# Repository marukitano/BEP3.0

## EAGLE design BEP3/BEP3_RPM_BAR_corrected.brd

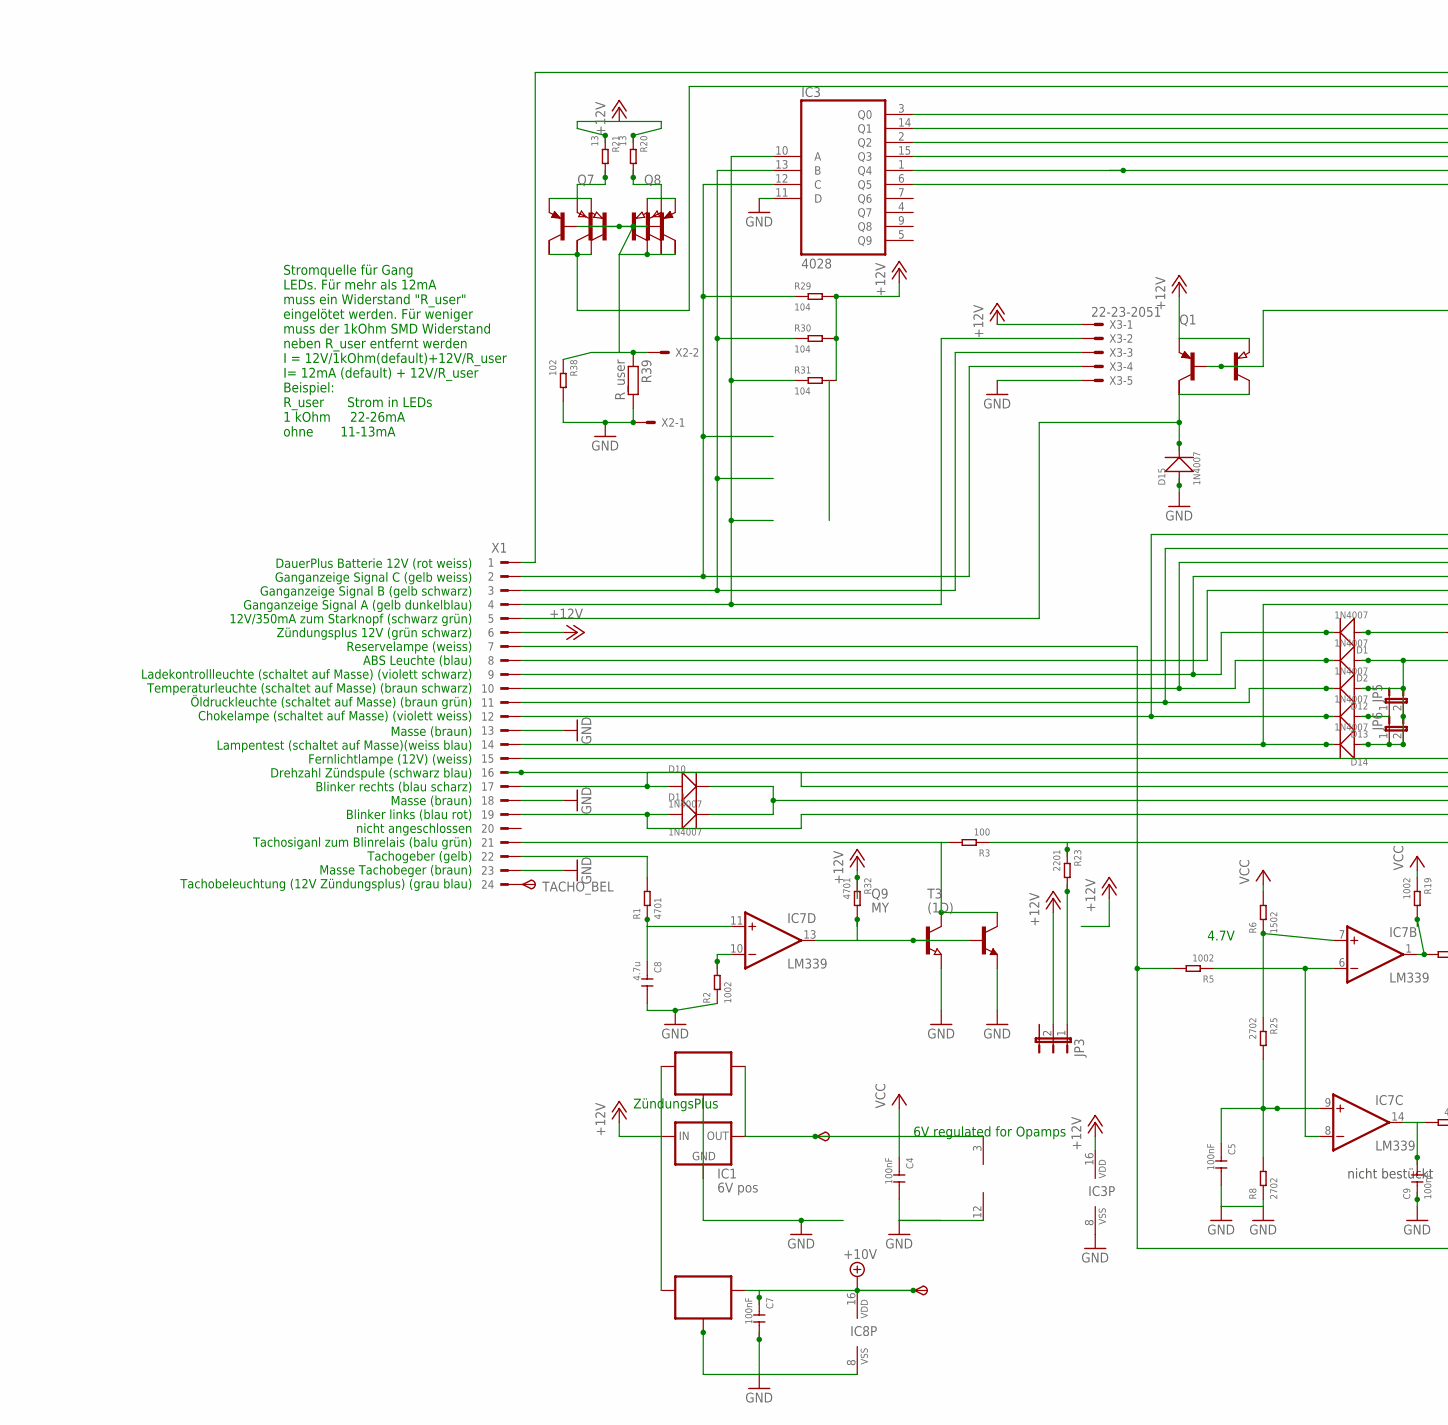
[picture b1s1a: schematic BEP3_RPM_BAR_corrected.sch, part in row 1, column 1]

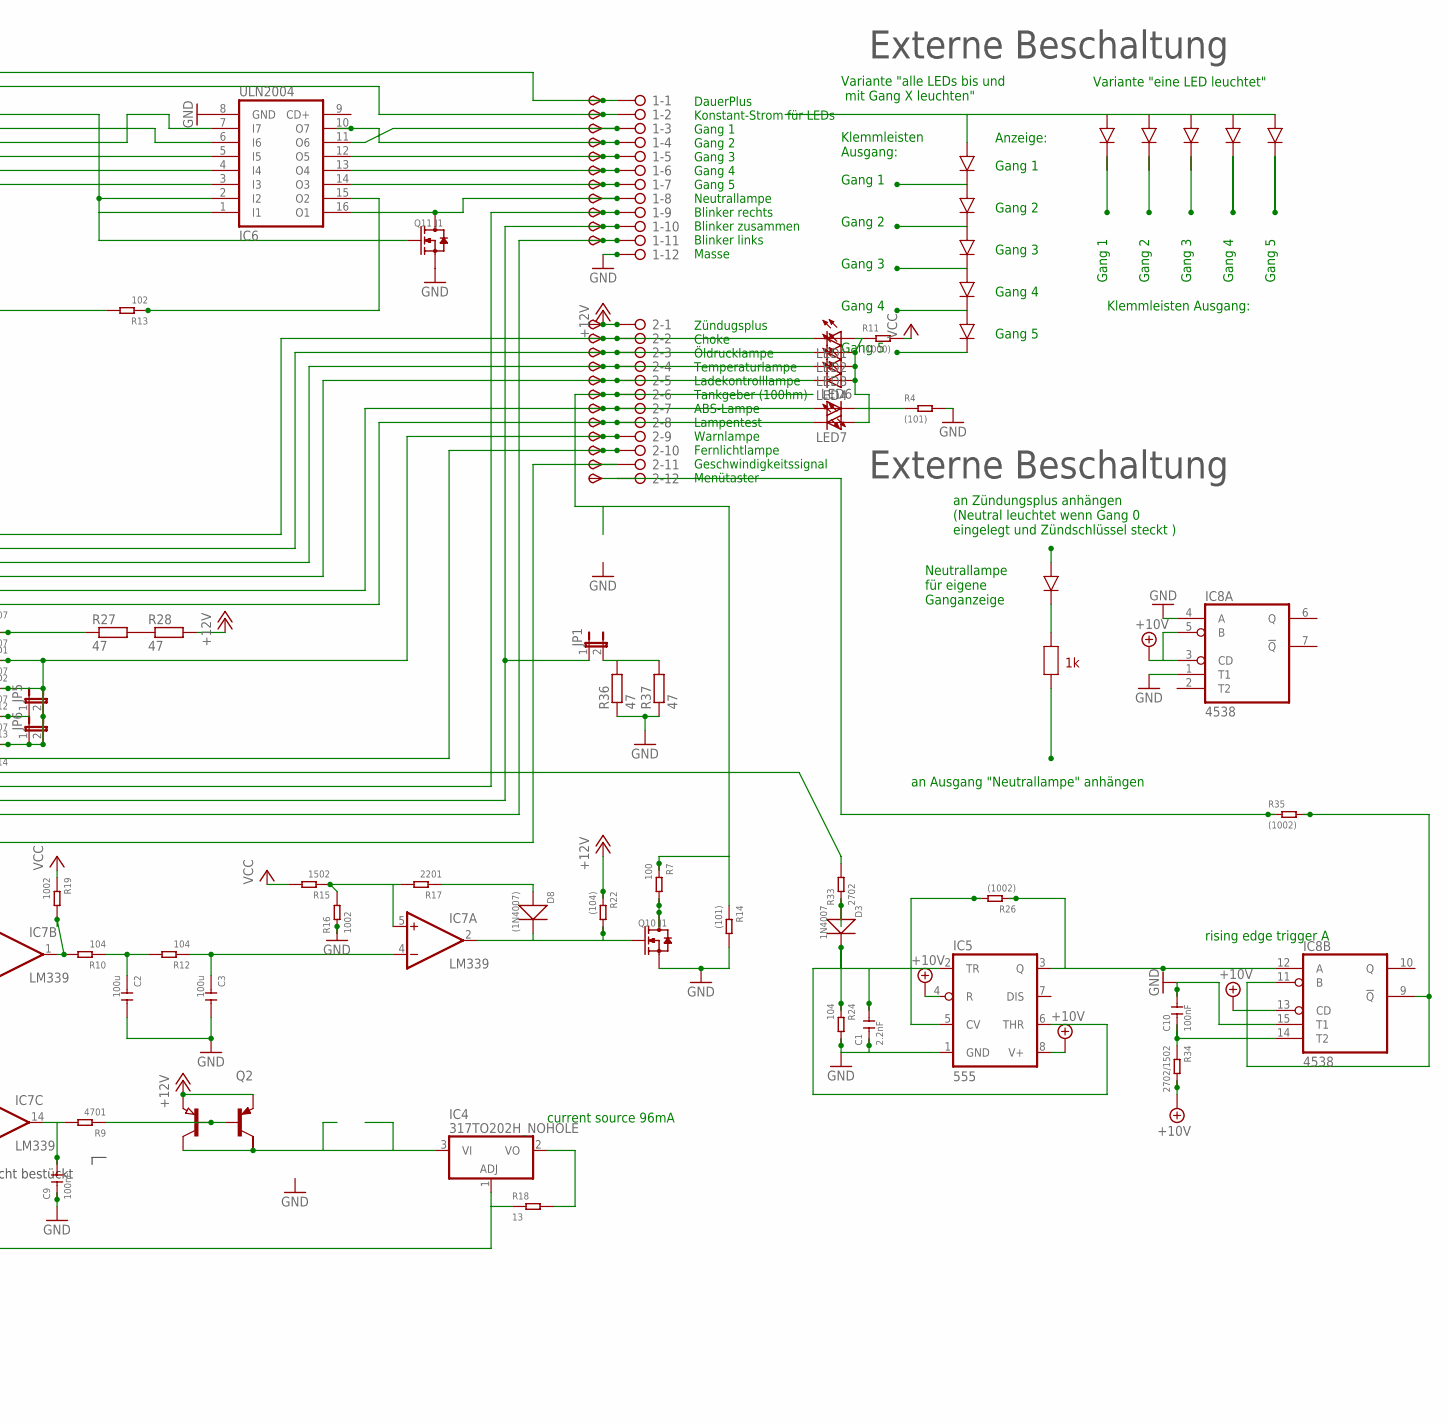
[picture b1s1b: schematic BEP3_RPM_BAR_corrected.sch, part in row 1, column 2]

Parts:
1, 2: 2081-1132; 12-PIN
6V, 10V: TPSB1.8; B1.8
C1: 2.2nF; C0805
C2, C3: 100u; C1206
C4, C5, C7, C9, C10: 100nF; C0805
C8: 4.7u; C0805
D1, D3, D10, D11, D15: 1N4007; DO-214AC
D2, D12, D13, D14: 1N4007; DO-214AC-1206MOUNT
D8: (1N4007); DO-214AC-1206MOUNT
IC1: 6V pos; 78LXX
IC2, IC9: 78LXXSOT89_ROUND; SOT89_ROUND
IC3: 4028; SO16
IC4: 317TO202H_NOHOLE; TO220H_NOHOLE
IC5: 555; SO08
IC6: ULN2004; SO16
IC7: LM339; SO14
IC8: 4538; SO16
JP1, JP5, JP6: JP1E; JP1
JP3: JP2E; JP2
LED1, LED2, LED3, LED4, LED6, LED7: LEDLD260; LD260
Q1, Q2, Q7, Q8: PNP-TRANSISTOR_SOT89; SOT89
Q3: AH-16; SOT223
Q4, Q5, Q6: (AH-16); SOT223
Q9: MY; SOT89
Q10, Q11: J1; SOT-23
R1, R9, R32: 4701; R0805
R2, R5, R16, R19: 1002; R0805
R3, R7: 100; R0805
R4, R14: (101); R0805
R6, R15: 1502; R0805
R8, R25, R33: 2702; R0805
R10, R12, R24, R29, R30, R31: 104; R0805
R11: (1000); R0805
R13, R38: 102; R0805
R17, R23: 2201; R0805
R18, R20, R21: 13; R1206
R22: (104); R0805
R26, R35: (1002); R0805
R27, R28, R36, R37: 47; V235/17_1MM
R34: 2702/1502; R0805
R39: R_user; R0805
T1: PNP2SM8; SM8
T3: (1D); SOT23-BEC
TACHO_BEL: TPSP1_1MM; P1_1.0MM
TP1, TP2, TP3, TP4, TP5, TP6, TP7, TP8, TP9, TP10, TP11, TP12, TP16, TP17, TP18, TP19, TP21, TP22, TP23, TP25, TP26: TPSB1.8; B1.8
TP13, TP24: TPSB1,27; B1,27
X1: CON_BMWV2; 24-PIN_V2
X2: 22-23-2021
X3: 22-23-2051

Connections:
+10V: 10V.TP, C7.1, IC5.4 (R), IC5.8 (V+), IC8.3 (CD), IC8.5 (B), IC8.13 (CD), IC8.16 (VDD), IC9.1 (OUT), R34.2
+12V: 2.1, IC1.IN, IC2.3 (IN), IC3.16 (VDD), IC9.3 (IN), JP3.2, Q1.3 (E), Q2.3 (E), Q3.3 (E), Q4.3 (E), R20.1, R21.1, R22.1, R28.2, R29.2, R30.2, R31.2, R32.1, TP12.TP, X1.6, X3.1
GND: 1.12, C1.1, C2.2, C3.2, C4.2, C5.2, C7.2, C8.2, C9.1, C10.2, D15.1 (+), IC1.GND, IC2.2 (GND), IC2.2@1 (GND), IC3.8 (VSS), IC3.11 (D), IC5.1 (GND), IC6.8 (GND), IC7.12 (GND), IC8.1 (T1), IC8.4 (A), IC8.8 (VSS), IC8.15 (T1), IC9.2 (GND), IC9.2@1 (GND), Q9.3 (E), Q10.2 (S), Q11.2 (S), R2.1, R4.2, R8.1, R14.2, R16.1, R24.2, R36.1, R37.1, R38.2, R39.2, T3.E, X1.13, X1.18, X1.23, X2.1, X3.5
unnamed: 2.9, D2.1 (+), D12.1 (+), D14.1 (+), JP5.2, JP6.1, JP6.2, TP24.TP
unnamed: IC3.10 (A), R31.1, X1.4, X3.2
unnamed: IC3.13 (B), R30.1, X1.3, X3.3
unnamed: 2.7, LED6.A, TP22.TP, X1.8
unnamed: Q5.3 (E), Q8.3 (E), R21.2, T1.1 (E)
unnamed: D8.2 (-), IC7.2 (OUT), Q10.1 (G), R22.2
unnamed: IC7.10 (-IN), R2.2
unnamed: R27.2, R28.1
unnamed: Q6.3 (E), Q7.3 (E), R20.2, T1.3 (E)
unnamed: D15.2 (-), Q1.2 (C), Q3.2 (C), X1.5
unnamed: 2.2, D13.2 (-), LED1.K (C), TP16.TP, X1.12
unnamed: 2.3, D12.2 (-), LED2.K (C), TP17.TP, X1.11
unnamed: 2.4, D2.2 (-), LED3.K (C), TP18.TP, X1.10
unnamed: IC4.3 (VI), Q2.2 (C), Q4.2 (C)
unnamed: IC7.6 (-IN), IC7.8 (-IN), R5.1
unnamed: IC3.12 (C), R29.1, X1.2, X3.4
unnamed: IC3.15 (Q3), IC6.5 (I5)
unnamed: 2.8, D14.2 (-), LED7.K (C), TP23.TP, X1.14
unnamed: 1.9, D10.1 (+), TP9.TP, X1.17
unnamed: 1.11, D11.1 (+), TP11.TP, X1.19
unnamed: IC8.9 (!Q), IC8.11 (B), R35.2
unnamed: R1.2, X1.22
unnamed: C8.1, IC7.11 (+IN), R1.1
unnamed: 1.6, IC6.13 (O4), TP6.TP
unnamed: 1.7, IC6.14 (O3), TP7.TP
unnamed: 2.11, R3.1, R23.1, TP26.TP
unnamed: 2.6, R7.1, R14.1, TP21.TP
unnamed: JP3.1, R23.2
unnamed: C5.1, IC7.9 (+IN), R8.2, R25.2
unnamed: C9.2, IC7.14 (OUT), R9.2
unnamed: C1.2, D3.2 (-), IC5.2 (TR), IC5.6 (THR), R24.1
unnamed: LED6.K (C), R4.1
unnamed: IC4.1 (ADJ), R5.2, R18.1, X1.7
unnamed: Q2.1 (B), Q4.1 (B), R9.1
unnamed: IC3.2 (Q2), IC6.7 (I7)
unnamed: 1.3, IC6.11 (O6), TP3.TP
unnamed: 1.5, IC6.12 (O5), TP5.TP
unnamed: LED1.A, LED2.A, LED3.A, LED4.A, LED7.A, R11.1
unnamed: R33.2, X1.16
unnamed: Q1.1 (B), Q3.1 (B), R13.2
unnamed: IC3.3 (Q0), IC6.1 (I1), IC6.2 (I2), Q11.1 (G)
unnamed: C2.1, R10.1, R12.2
unnamed: C3.1, IC7.4 (-IN), R12.1
unnamed: IC7.5 (+IN), R15.1, R16.2, R17.2
unnamed: Q10.3 (D), R7.2
unnamed: D8.1 (+), R17.1
unnamed: IC3.1 (Q4), IC6.4 (I4)
unnamed: 1.8, IC6.16 (O1), Q11.3 (D), TP8.TP
unnamed: 2.10, TP25.TP, X1.15
unnamed: D1.1 (+), R27.1
unnamed: 2.5, D1.2 (-), LED4.K (C), TP19.TP, X1.9
unnamed: IC3.14 (Q1), IC6.6 (I6)
unnamed: Q5.1 (B), Q6.1 (B), Q6.2 (C), Q7.1 (B), Q7.2 (C), Q8.1 (B), R38.1, R39.1, T1.2 (B), T1.4 (B), T1.6 (C1), X2.2
unnamed: TACHO_BEL.TP, X1.24
unnamed: 1.2, Q5.2 (C), Q8.2 (C), T1.8 (C1), TP2.TP
unnamed: IC3.6 (Q5), IC6.3 (I3)
unnamed: IC4.2 (VO), R18.2
unnamed: IC5.5 (CV), R26.2
unnamed: 1.4, IC6.10 (O7), TP4.TP
unnamed: 1.1, TP1.TP, X1.1
unnamed: IC7.7 (+IN), R6.1, R25.1
unnamed: Q9.2 (C), R3.2, T3.C, X1.21
unnamed: IC7.13 (OUT), Q9.1 (B), R32.2, T3.B
unnamed: IC5.3 (Q), IC8.12 (A), R26.1
unnamed: D3.1 (+), R33.1
unnamed: IC6.15 (O2), R13.1
unnamed: C10.1, IC8.14 (T2), R34.1
unnamed: 2.12, R35.1, TP13.TP
unnamed: 1.10, D10.2 (-), D11.2 (-), JP1.1, TP10.TP
unnamed: JP1.2, R36.2, R37.2
unnamed: D13.1 (+), JP5.1
unnamed: IC7.1 (OUT), R10.2, R19.2
VCC: 6V.TP, C4.1, IC1.OUT, IC2.1 (OUT), IC7.3 (V+), R6.2, R11.2, R15.2, R19.1

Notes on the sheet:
6V regulated for Opamps
current source 96mA
ZündungsPlus
Zündugsplus Choke Öldrucklampe Temperaturlampe Ladekontrolllampe Tankgeber (100hm) ABS-Lampe Lampentest Warnlampe Fernlichtlampe Geschwindigkeitssignal Menütaster
DauerPlus Konstant-Strom für LEDs Gang 1 Gang 2 Gang 3 Gang 4 Gang 5 Neutrallampe Blinker rechts Blinker zusammen Blinker links Masse
DauerPlus Batterie 12V (rot weiss) Ganganzeige Signal C (gelb weiss) Ganganzeige Signal B (gelb schwarz) Ganganzeige Signal A (gelb dunkelblau) 12V/350mA zum Starknopf (schwarz grün) Zündungsplus 12V (grün schwarz) Reservelampe (weiss) ABS Leuchte (blau) Ladekontrollleuchte (schaltet auf Masse) (vi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
Masse (braun) Lampentest (schaltet auf Masse)(weiss blau) Fernlichtlampe (12V) (weiss) Drehzahl Zündspule (schwarz blau) Blinker rechts (blau scharz) Masse (braun) Blinker links (blau rot) nicht angeschlossen Tachosiganl zum Blinrelais (balu grün) Tachogeber (gelb) Masse Tachobeger (braun) Tachobel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
4.7V
Stromquelle für Gang LEDs. Für mehr als 12mA muss ein Widerstand "R_user" eingelötet werden. Für weniger muss der 1kOhm SMD Widerstand neben R_user entfernt werden I = 12V/1kOhm(default)+12V/R_user I= 12mA (default) + 12V/R_user Beispiel: R_user Strom in LEDs 1 kOhm 22-26mA ohne 11-13mA
Gang 1
Gang 2
Gang 3
Gang 4
Gang 5
Variante "eine LED leuchtet"
Variante "alle LEDs bis und mit Gang X leuchten"
Klemmleisten Ausgang:
Klemmleisten Ausgang:
an Zündungsplus anhängen (Neutral leuchtet wenn Gang 0 eingelegt und Zündschlüssel steckt )
an Ausgang "Neutrallampe" anhängen
Neutrallampe für eigene Ganganzeige
Externe Beschaltung
Anzeige:
nicht bestückt
rising edge trigger A

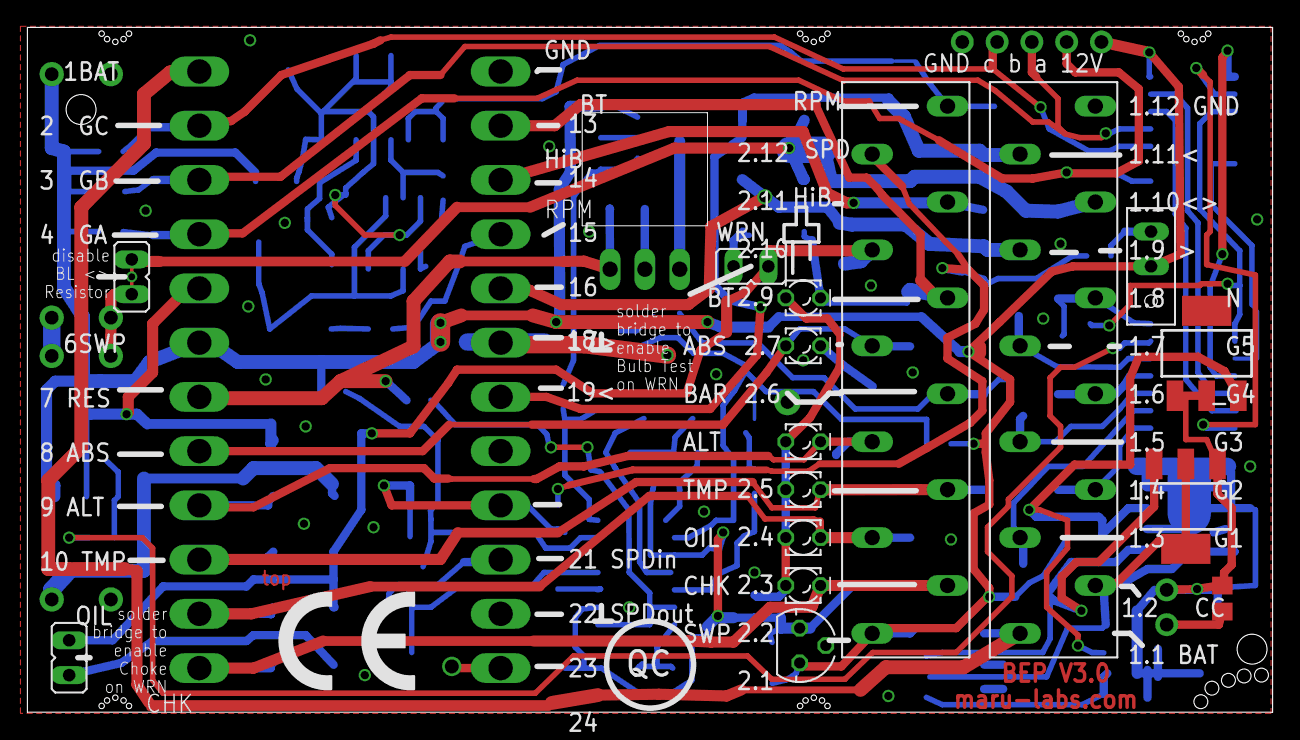
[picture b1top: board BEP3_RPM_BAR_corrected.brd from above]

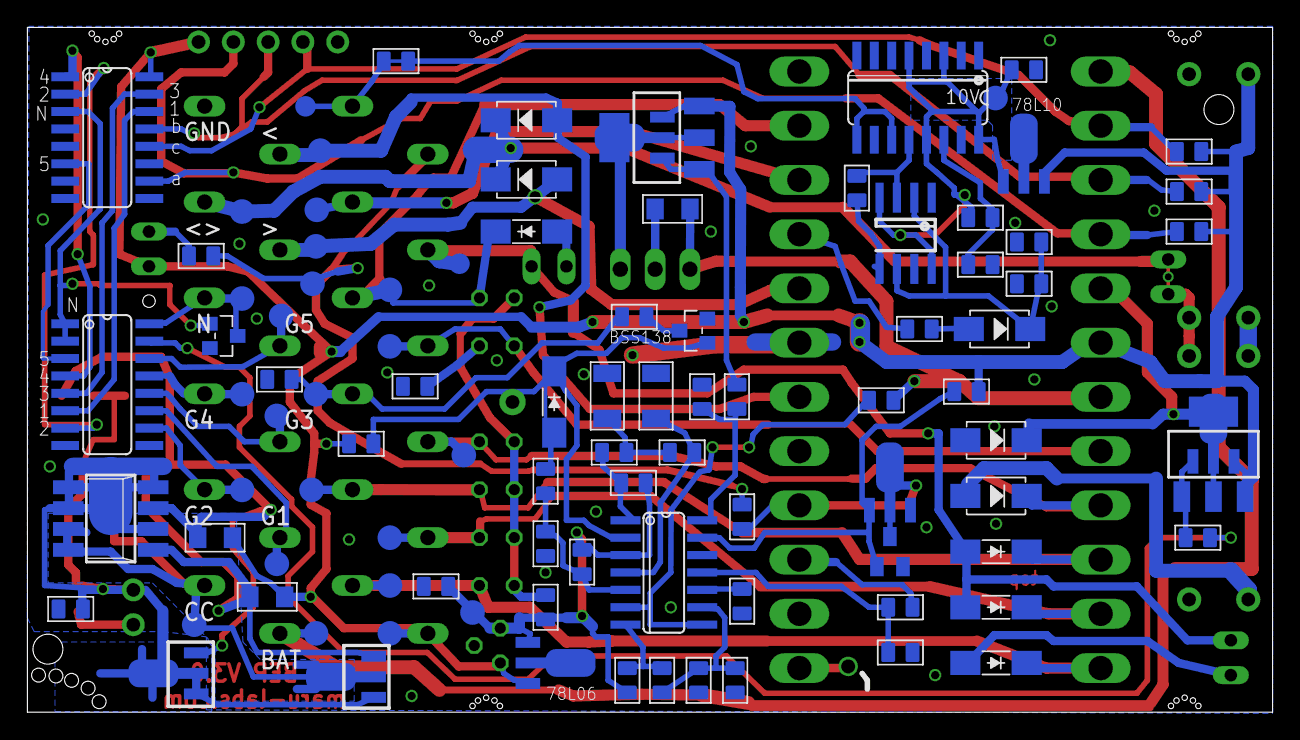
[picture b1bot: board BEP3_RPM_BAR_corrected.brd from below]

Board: 2 copper layers, 90.9 x 50.0 mm, 122 parts (97 on the bottom side), 76 nets.

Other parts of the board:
U$1: CE_10.00

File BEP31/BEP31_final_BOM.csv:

"Qty";"Value";"Device";"Package";"Parts";"Description";"MF";"MPN";"OC_FARNELL";"OC_NEWARK";"TP";"TP_SIGNAL_NAME";"VALUE";
"2";"";"2081-1132";"12-PIN";"1, 2";"WAGO SREW CLAMP";"";"";"";"";"";"";"";
"2";"";"78LXXSOT89_ROUND";"SOT89_ROUND";"IC2, IC9";"";"";"";"";"";"";"";"";
"1";"";"CON_BMWV2";"24-PIN_V2";"X1";"BMW CONNECTOR";"";"";"";"";"";"";"";
"4";"";"JP2EJP2_SMALLPADS";"JP2_SMALLPADS";"JP1, JP2, JP3, JP4";"JUMPER";"";"";"";"";"";"";"";
"6";"";"LEDLD260";"LD260";"LED1, LED2, LED3, LED4, LED6, LED7";"LED";"";"";"";"";"";"";"";
"4";"";"PNP-TRANSISTOR_SOT89";"SOT89";"Q1, Q2, Q7, Q8";"PNP TRANSISTOR";"";"";"";"";"";"";"";
"1";"(1000)";"SMD-RES-100R-5%-1/8W(0805)";"R0805";"R11";"301010319";"";"RC0805JR-07100RL";"";"";"";"";"100R";
"1";"(1002)";"SMD-RES-4.7K-5%-1/8W(0805)";"R0805";"R35";"301010306";"";"RC0805JR-074K7L";"";"";"";"";"4.7K";
"1";"(101)";"SMD-RES-100R-5%-1/8W(0805)";"R0805";"R4";"301010319";"";"RC0805JR-07100RL";"";"";"";"";"100R";
"1";"(101)";"SMD-RES-2.2K-5%-1/8W(0805)";"R0805";"R14";"301010333";"";"RC0805JR-072K2L";"";"";"";"";"2.2K";
"1";"100";"SMD-RES-2.2K-5%-1/8W(0805)";"R0805";"R7";"301010333";"";"RC0805JR-072K2L";"";"";"";"";"2.2K";
"1";"100";"SMD-RES-220R-5%-1/8W(0805)";"R0805";"R3";"301010315";"";"RC0805JR-07220RL";"";"";"";"";"220R";
"5";"1002";"SMD-RES-10K-1%-1/8W(0805)";"R0805";"R2, R5, R16, R19, R42";"301010361";"";"RC0805FR-0710KL";"";"";"";"";"10K";
"6";"100nF";"CERAMIC-100NF-50V-10%-X7R(0805)";"C0805";"C4, C5, C7, C9, C10, C11";"302010165";"";"CC0805KRX7R9BB104";"";"";"";"";"100nf";
"2";"100u";"CERAMIC-100UF-6.3V-20%-X5R(1206)";"C1206";"C2, C3";"302010183";"";"GRM31CR60J107ME39L";"";"";"";"";"100uf";
"5";"102";"SMD-RES-1K-5%-1/8W(0805)";"R0805";"R13, R38, R43, R45, R46";"301010311";"";"RC0805JR-071KL";"";"";"";"";"1K";
"7";"104";"SMD-RES-10K-1%-1/8W(0805)";"R0805";"R10, R12, R22, R24, R29, R30, R31";"301010361";"";"RC0805FR-0710KL";"";"";"";"";"10K";
"3";"13";"SMD-RES-13R-5%-1/4W(1206)";"R1206";"R18, R20, R21";"301010405";"";"RC1206JR-0713RL";"";"";"";"";"13R";
"2";"1502";"SMD-RES-10K-1%-1/8W(0805)";"R0805";"R6, R15";"301010361";"";"RC0805FR-0710KL";"";"";"";"";"10K";
"6";"1N4007";"DIODE-GEN-PURPOSE-1KV-1A(DO-214AC)";"DO-214AC";"D1, D3, D8, D10, D11, D15";"304010013";"";"1N4007";"";"";"";"";"1N4007";
"4";"1N4007";"DIODE-GEN-PURPOSE-1KV-1A(DO-214AC)DO-214AC/1206";"DO-214AC-1206MOUNT";"D2, D12, D13, D14";"304010013";"";"";"";"";"";"";"";
"1";"2.2nF";"CERAMIC-100NF-50V-10%-X7R(0805)";"C0805";"C1";"302010165";"";"CC0805KRX7R9BB104";"";"";"";"";"100nf";
"1";"22-23-2021";"22-23-2021";"22-23-2021";"X2";".100" (2.54mm) Center Header - 2 Pin";"MOLEX";"22-23-2021";"1462926";"25C3832";"";"";"";
"1";"22-23-2051";"22-23-2051";"22-23-2051";"X3";".100" (2.54mm) Center Header - 5 Pin";"MOLEX";"22-23-2051";"1462952";"38C9178";"";"";"";
"2";"2201";"SMD-RES-2.2K-5%-1/8W(0805)";"R0805";"R17, R23";"301010333";"";"RC0805JR-072K2L";"";"";"";"";"2.2K";
"1";"2702";"SMD-RES-10K-1%-1/8W(0805)";"R0805";"R33";"301010361";"";"RC0805FR-0710KL";"";"";"";"";"10K";
"3";"2702";"SMD-RES-4.7K-5%-1/8W(0805)";"R0805";"R8, R25, R44";"301010306";"";"RC0805JR-074K7L";"";"";"";"";"4.7K";
"1";"2702/1502";"SMD-RES-4.7K-5%-1/8W(0805)";"R0805";"R34";"301010306";"";"RC0805JR-074K7L";"";"";"";"";"4.7K";
"1";"317TO202H_NOHOLE";"317TO202H_NOHOLE";"TO220H_NOHOLE";"IC4";"Positive VOLTAGE REGULATOR";"";"";"";"";"";"";"";
"1";"4.7u";"CERAMIC-4.7UF-25V-10%-X5R(0805)";"C0805";"C8";"302010146";"";"CC0805KKX5R8BB475";"";"";"";"";"4.7uf";
"1";"4028";"4028D";"SO16";"IC3";"BCD to decimal DECODER";"";"";"";"";"";"";"";
"1";"4538";"4538D";"SO16";"IC8";"Dual precision monostable MULTIVIBRATOR";"";"";"";"";"";"";"";
"4";"47";"R-EU_V235/17_1MM";"V235/17_1MM";"R27, R28, R36, R37";"RESISTOR, European symbol";"";"";"";"";"";"";"";
"3";"4701";"SMD-RES-4.7K-5%-1/8W(0805)";"R0805";"R1, R9, R32";"301010306";"";"RC0805JR-074K7L";"";"";"";"";"4.7K";
"1";"555";"NE555D";"SO08";"IC5";"TIMER";"";"";"";"";"";"";"";
"1";"6V pos";"78LXX";"78LXX";"IC1";"VOLTAGE REGULATOR";"";"";"";"";"";"";"";
"2";"J1";"SMD-MOSFET-N-CH-50V-200MA-BSS138W-7-F(SOT-23)";"SOT-23";"Q10, Q11";"305030000";"";"BSS138W-7-F";"";"";"";"";"BSS138W-7-F";
"1";"JP2E_ORIG";"JP2E_ORIG";"JP2_ORIG_SMALLPADS";"U$2";"";"";"";"";"";"";"";"";
"1";"LM2904";"LM358D";"SO08";"IC10";"OP AMP also LM158; LM258; LM2904";"";"";"";"";"";"";"";
"1";"LM339";"LM339D";"SO14";"IC7";"Low Power Low Offset Voltage Quad Comparators";"";"";"";"";"";"";"";
"1";"MY";"NPN-TRANSISTOR_SOT89";"SOT89";"Q9";"NPN TRANSISTOR";"";"";"";"";"";"";"";
"1";"NUP4304SOT457_R";"NUP4304SOT457_R";"SOT457R_PHILIPS";"U$3";"";"";"";"";"";"";"";"";
"1";"SM6T";"SM6T";"DO214AA";"D4";"Z DIODE";"";"";"";"";"";"";"";
"1";"TPSB1,27";"TPSB1,27";"B1,27";"TP24";"TEST PIN";"";"";"";"";"";"";"";
"25";"TPSB2.0";"TPSB2.0";"B2.0";"6V, 10V, START, TP1, TP2, TP3, TP4, TP5, TP6, TP7, TP8, TP9, TP10, TP11, TP12, TP13, TP16, TP17, TP18, TP19, TP21, TP22, TP23, TP25, TP26";"TEST PIN";"";"";"";"";"";"";"";
"1";"ULN2004";"ULN2004AD";"SO16";"IC6";"DRIVER ARRAY";"";"";"";"";"";"";"";

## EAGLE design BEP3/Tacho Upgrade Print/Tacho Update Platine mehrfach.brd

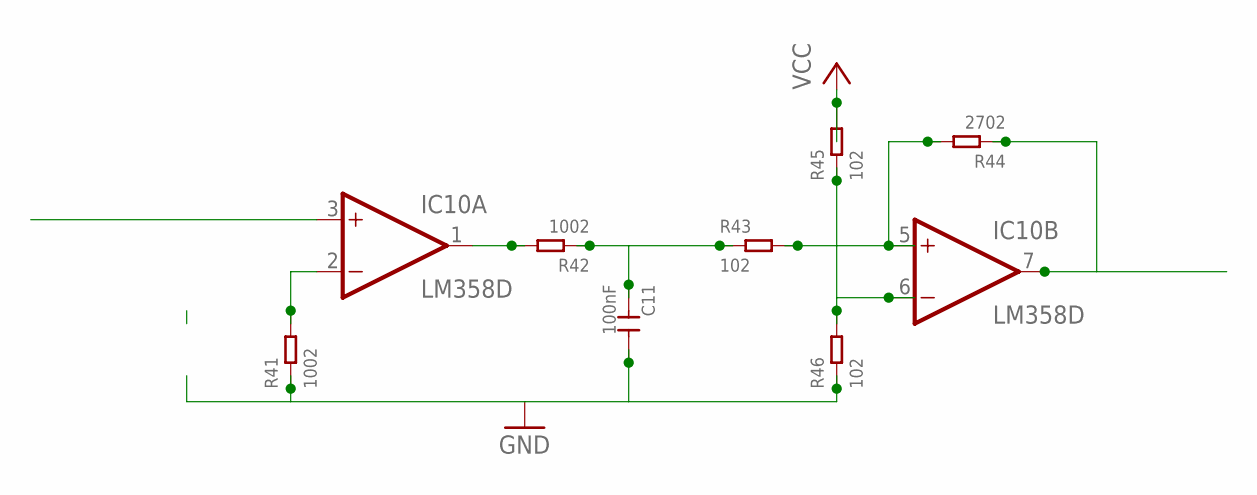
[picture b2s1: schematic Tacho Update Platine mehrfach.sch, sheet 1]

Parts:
C11: 100nF; C0805
IC10: LM358D; SO08
R41, R42: 1002; R0805
R43, R45, R46: 102; R0805
R44: 2702; R0805

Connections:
GND: C11.2, R41.1, R46.1; also elsewhere on the board
unnamed: IC10.1 (OUT), R42.2
unnamed: C11.1, R42.1, R43.1
unnamed: IC10.5 (+IN), R43.2, R44.2
unnamed: IC10.6 (-IN), R45.1, R46.2
unnamed: IC10.2 (-IN), R41.2
unnamed: IC10.7 (OUT), R44.1
V+: IC10.8 (V+)
V-: IC10.4 (V-)
VCC: R45.2; also elsewhere on the board

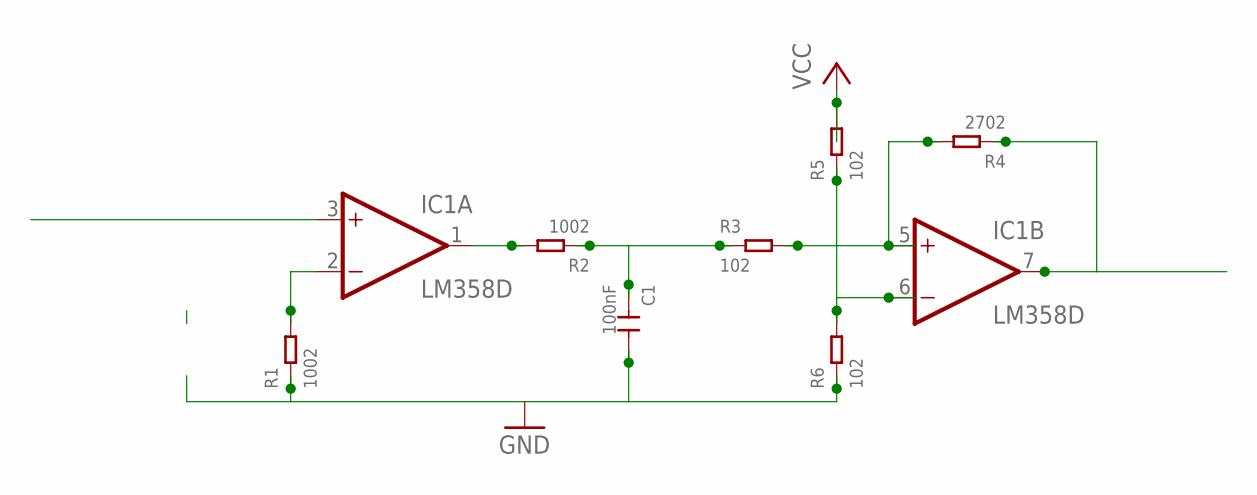
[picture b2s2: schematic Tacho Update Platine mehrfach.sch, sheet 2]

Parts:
C1: 100nF; C0805
IC1: LM358D; SO08
R1, R2: 1002; R0805
R3, R5, R6: 102; R0805
R4: 2702; R0805

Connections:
GND: C1.2, R1.1, R6.1; also elsewhere on the board
unnamed: IC1.1 (OUT), R2.2
unnamed: C1.1, R2.1, R3.1
unnamed: IC1.5 (+IN), R3.2, R4.2
unnamed: IC1.6 (-IN), R5.1, R6.2
unnamed: IC1.2 (-IN), R1.2
unnamed: IC1.7 (OUT), R4.1
V+1: IC1.8 (V+)
V-1: IC1.4 (V-)
VCC: R5.2; also elsewhere on the board

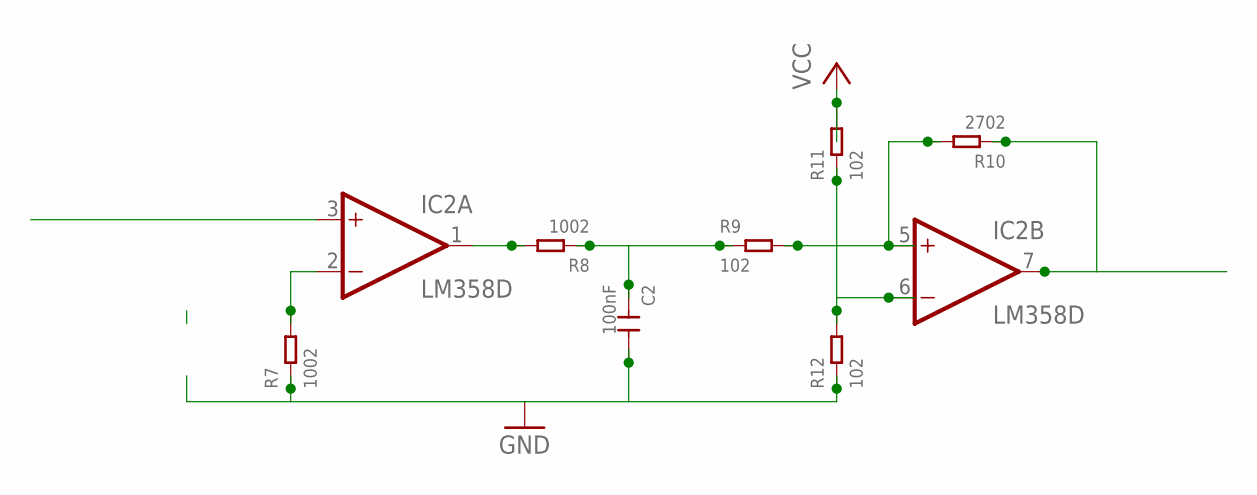
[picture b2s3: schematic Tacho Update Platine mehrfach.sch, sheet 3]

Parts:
C2: 100nF; C0805
IC2: LM358D; SO08
R7, R8: 1002; R0805
R9, R11, R12: 102; R0805
R10: 2702; R0805

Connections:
GND: C2.2, R7.1, R12.1; also elsewhere on the board
unnamed: IC2.1 (OUT), R8.2
unnamed: C2.1, R8.1, R9.1
unnamed: IC2.5 (+IN), R9.2, R10.2
unnamed: IC2.6 (-IN), R11.1, R12.2
unnamed: IC2.2 (-IN), R7.2
unnamed: IC2.7 (OUT), R10.1
V+2: IC2.8 (V+)
V-2: IC2.4 (V-)
VCC: R11.2; also elsewhere on the board

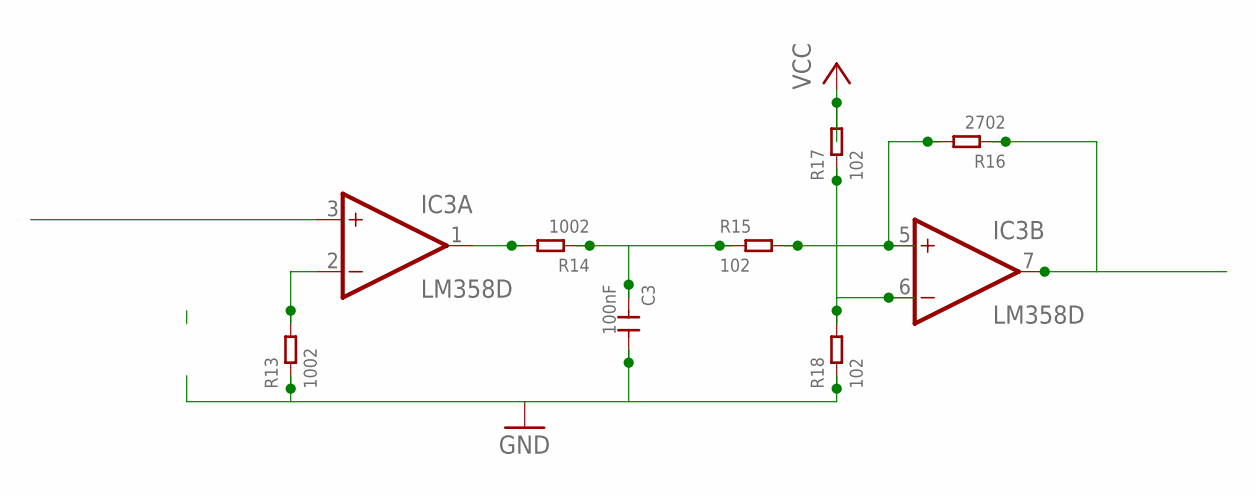
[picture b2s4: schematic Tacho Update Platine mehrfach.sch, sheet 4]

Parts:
C3: 100nF; C0805
IC3: LM358D; SO08
R13, R14: 1002; R0805
R15, R17, R18: 102; R0805
R16: 2702; R0805

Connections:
GND: C3.2, R13.1, R18.1; also elsewhere on the board
unnamed: IC3.1 (OUT), R14.2
unnamed: C3.1, R14.1, R15.1
unnamed: IC3.5 (+IN), R15.2, R16.2
unnamed: IC3.6 (-IN), R17.1, R18.2
unnamed: IC3.2 (-IN), R13.2
unnamed: IC3.7 (OUT), R16.1
V+3: IC3.8 (V+)
V-3: IC3.4 (V-)
VCC: R17.2; also elsewhere on the board

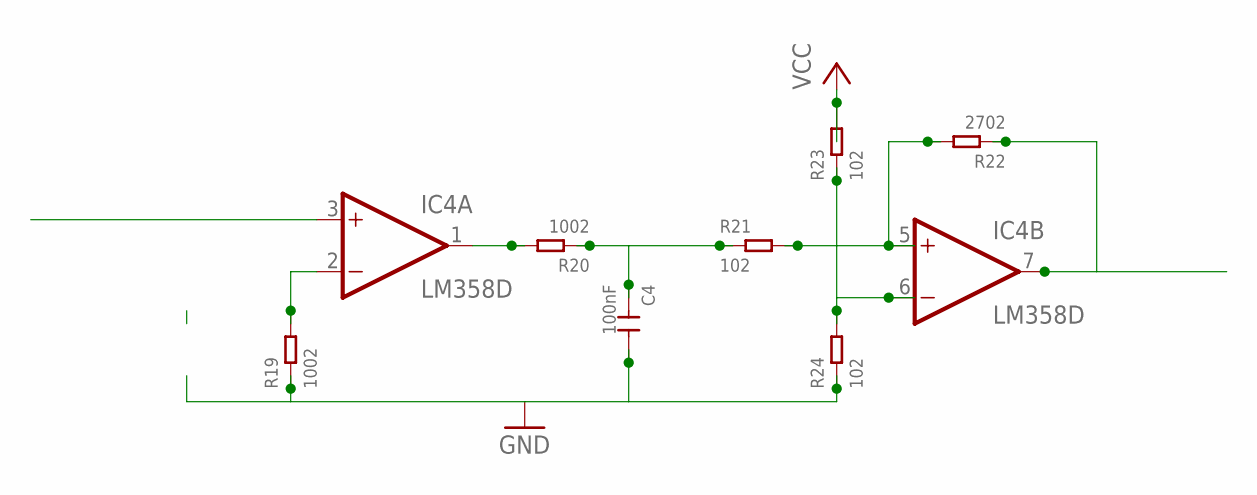
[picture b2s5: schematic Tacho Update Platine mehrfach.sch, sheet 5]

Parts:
C4: 100nF; C0805
IC4: LM358D; SO08
R19, R20: 1002; R0805
R21, R23, R24: 102; R0805
R22: 2702; R0805

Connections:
GND: C4.2, R19.1, R24.1; also elsewhere on the board
unnamed: IC4.1 (OUT), R20.2
unnamed: C4.1, R20.1, R21.1
unnamed: IC4.5 (+IN), R21.2, R22.2
unnamed: IC4.6 (-IN), R23.1, R24.2
unnamed: IC4.2 (-IN), R19.2
unnamed: IC4.7 (OUT), R22.1
V+4: IC4.8 (V+)
V-4: IC4.4 (V-)
VCC: R23.2; also elsewhere on the board

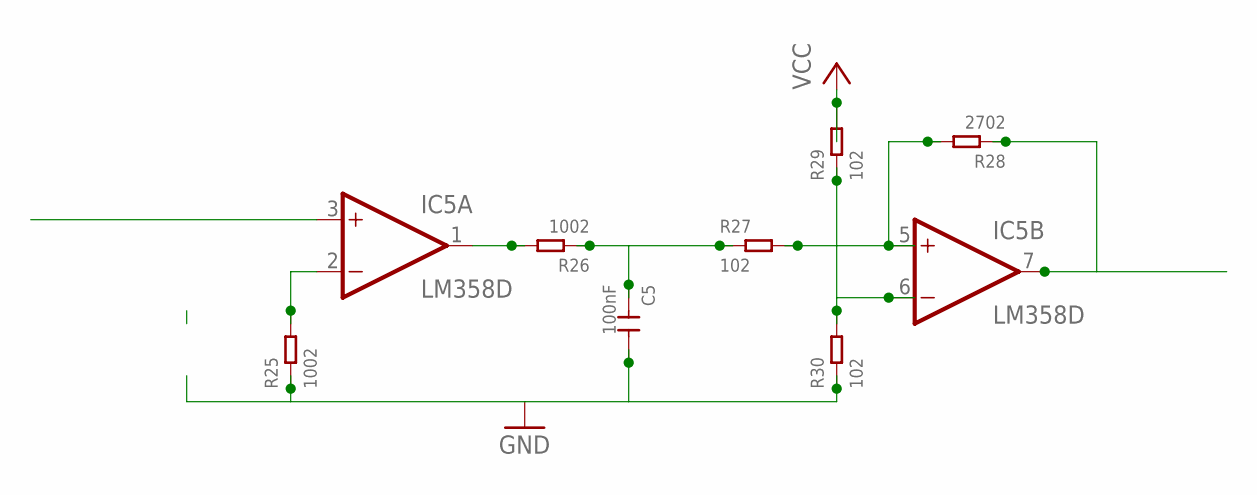
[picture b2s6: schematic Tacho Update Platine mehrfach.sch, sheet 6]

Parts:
C5: 100nF; C0805
IC5: LM358D; SO08
R25, R26: 1002; R0805
R27, R29, R30: 102; R0805
R28: 2702; R0805

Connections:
GND: C5.2, R25.1, R30.1; also elsewhere on the board
unnamed: IC5.1 (OUT), R26.2
unnamed: C5.1, R26.1, R27.1
unnamed: IC5.5 (+IN), R27.2, R28.2
unnamed: IC5.6 (-IN), R29.1, R30.2
unnamed: IC5.2 (-IN), R25.2
unnamed: IC5.7 (OUT), R28.1
V+5: IC5.8 (V+)
V-5: IC5.4 (V-)
VCC: R29.2; also elsewhere on the board

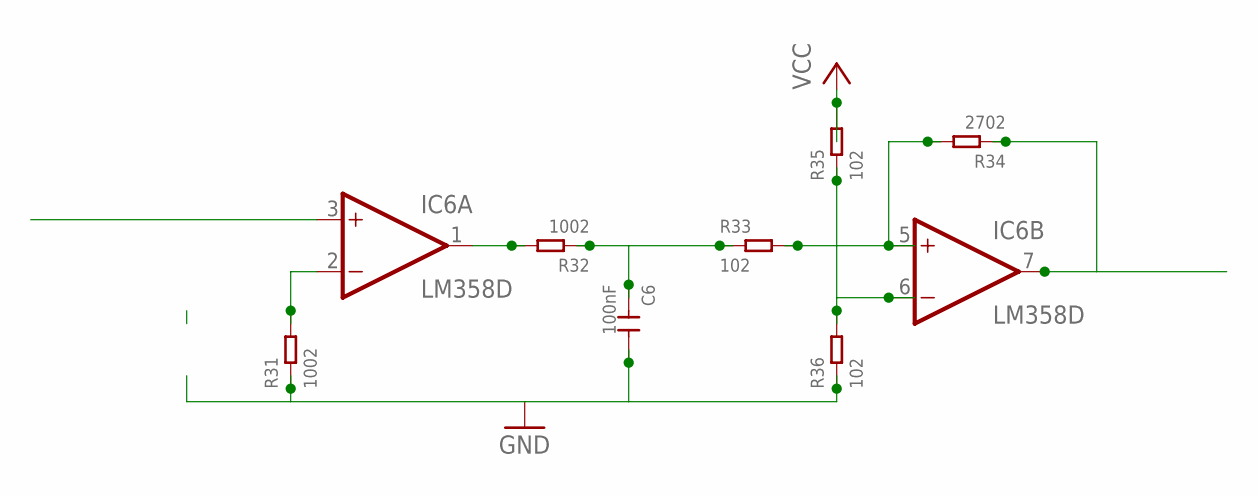
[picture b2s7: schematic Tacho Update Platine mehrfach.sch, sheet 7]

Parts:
C6: 100nF; C0805
IC6: LM358D; SO08
R31, R32: 1002; R0805
R33, R35, R36: 102; R0805
R34: 2702; R0805

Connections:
GND: C6.2, R31.1, R36.1; also elsewhere on the board
unnamed: IC6.1 (OUT), R32.2
unnamed: C6.1, R32.1, R33.1
unnamed: IC6.5 (+IN), R33.2, R34.2
unnamed: IC6.6 (-IN), R35.1, R36.2
unnamed: IC6.2 (-IN), R31.2
unnamed: IC6.7 (OUT), R34.1
V+6: IC6.8 (V+)
V-6: IC6.4 (V-)
VCC: R35.2; also elsewhere on the board

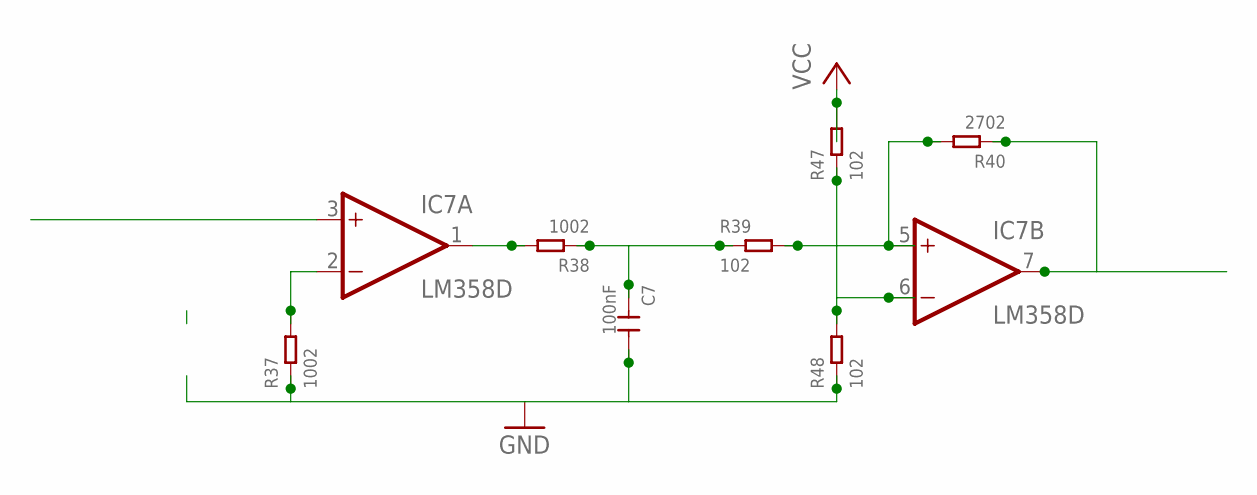
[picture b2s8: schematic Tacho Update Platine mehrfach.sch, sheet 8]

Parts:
C7: 100nF; C0805
IC7: LM358D; SO08
R37, R38: 1002; R0805
R39, R47, R48: 102; R0805
R40: 2702; R0805

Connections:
GND: C7.2, R37.1, R48.1; also elsewhere on the board
unnamed: IC7.1 (OUT), R38.2
unnamed: C7.1, R38.1, R39.1
unnamed: IC7.5 (+IN), R39.2, R40.2
unnamed: IC7.6 (-IN), R47.1, R48.2
unnamed: IC7.2 (-IN), R37.2
unnamed: IC7.7 (OUT), R40.1
V+7: IC7.8 (V+)
V-7: IC7.4 (V-)
VCC: R47.2; also elsewhere on the board

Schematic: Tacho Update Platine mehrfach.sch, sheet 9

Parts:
C8: 100nF; C0805
IC8: LM358D; SO08
R49, R50: 1002; R0805
R51, R53, R54: 102; R0805
R52: 2702; R0805

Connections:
GND: C8.2, R49.1, R54.1; also elsewhere on the board
unnamed: IC8.1 (OUT), R50.2
unnamed: C8.1, R50.1, R51.1
unnamed: IC8.5 (+IN), R51.2, R52.2
unnamed: IC8.6 (-IN), R53.1, R54.2
unnamed: IC8.2 (-IN), R49.2
unnamed: IC8.7 (OUT), R52.1
V+8: IC8.8 (V+)
V-8: IC8.4 (V-)
VCC: R53.2; also elsewhere on the board

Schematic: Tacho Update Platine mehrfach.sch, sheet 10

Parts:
C9: 100nF; C0805
IC9: LM358D; SO08
R55, R56: 1002; R0805
R57, R59, R60: 102; R0805
R58: 2702; R0805

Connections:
GND: C9.2, R55.1, R60.1; also elsewhere on the board
unnamed: IC9.1 (OUT), R56.2
unnamed: C9.1, R56.1, R57.1
unnamed: IC9.5 (+IN), R57.2, R58.2
unnamed: IC9.6 (-IN), R59.1, R60.2
unnamed: IC9.2 (-IN), R55.2
unnamed: IC9.7 (OUT), R58.1
V+9: IC9.8 (V+)
V-9: IC9.4 (V-)
VCC: R59.2; also elsewhere on the board

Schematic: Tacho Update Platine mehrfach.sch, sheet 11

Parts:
C10: 100nF; C0805
IC11: LM358D; SO08
R61, R62: 1002; R0805
R63, R65, R66: 102; R0805
R64: 2702; R0805

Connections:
GND: C10.2, R61.1, R66.1; also elsewhere on the board
unnamed: IC11.1 (OUT), R62.2
unnamed: C10.1, R62.1, R63.1
unnamed: IC11.5 (+IN), R63.2, R64.2
unnamed: IC11.6 (-IN), R65.1, R66.2
unnamed: IC11.2 (-IN), R61.2
unnamed: IC11.7 (OUT), R64.1
V+10: IC11.8 (V+)
V-10: IC11.4 (V-)
VCC: R65.2; also elsewhere on the board

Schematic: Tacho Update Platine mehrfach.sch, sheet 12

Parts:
C12: 100nF; C0805
IC12: LM358D; SO08
R67, R68: 1002; R0805
R69, R71, R72: 102; R0805
R70: 2702; R0805

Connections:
GND: C12.2, R67.1, R72.1; also elsewhere on the board
unnamed: IC12.1 (OUT), R68.2
unnamed: C12.1, R68.1, R69.1
unnamed: IC12.5 (+IN), R69.2, R70.2
unnamed: IC12.6 (-IN), R71.1, R72.2
unnamed: IC12.2 (-IN), R67.2
unnamed: IC12.7 (OUT), R70.1
V+11: IC12.8 (V+)
V-11: IC12.4 (V-)
VCC: R71.2; also elsewhere on the board

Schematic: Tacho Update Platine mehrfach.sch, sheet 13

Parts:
C13: 100nF; C0805
IC13: LM358D; SO08
R73, R74: 1002; R0805
R75, R77, R78: 102; R0805
R76: 2702; R0805

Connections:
GND: C13.2, R73.1, R78.1; also elsewhere on the board
unnamed: IC13.1 (OUT), R74.2
unnamed: C13.1, R74.1, R75.1
unnamed: IC13.5 (+IN), R75.2, R76.2
unnamed: IC13.6 (-IN), R77.1, R78.2
unnamed: IC13.2 (-IN), R73.2
unnamed: IC13.7 (OUT), R76.1
V+12: IC13.8 (V+)
V-12: IC13.4 (V-)
VCC: R77.2; also elsewhere on the board

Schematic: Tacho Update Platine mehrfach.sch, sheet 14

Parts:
C14: 100nF; C0805
IC14: LM358D; SO08
R79, R80: 1002; R0805
R81, R83, R84: 102; R0805
R82: 2702; R0805

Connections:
GND: C14.2, R79.1, R84.1; also elsewhere on the board
unnamed: IC14.1 (OUT), R80.2
unnamed: C14.1, R80.1, R81.1
unnamed: IC14.5 (+IN), R81.2, R82.2
unnamed: IC14.6 (-IN), R83.1, R84.2
unnamed: IC14.2 (-IN), R79.2
unnamed: IC14.7 (OUT), R82.1
V+13: IC14.8 (V+)
V-13: IC14.4 (V-)
VCC: R83.2; also elsewhere on the board

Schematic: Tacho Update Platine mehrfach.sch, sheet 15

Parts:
C15: 100nF; C0805
IC15: LM358D; SO08
R85, R86: 1002; R0805
R87, R89, R90: 102; R0805
R88: 2702; R0805

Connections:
GND: C15.2, R85.1, R90.1; also elsewhere on the board
unnamed: IC15.1 (OUT), R86.2
unnamed: C15.1, R86.1, R87.1
unnamed: IC15.5 (+IN), R87.2, R88.2
unnamed: IC15.6 (-IN), R89.1, R90.2
unnamed: IC15.2 (-IN), R85.2
unnamed: IC15.7 (OUT), R88.1
V+14: IC15.8 (V+)
V-14: IC15.4 (V-)
VCC: R89.2; also elsewhere on the board

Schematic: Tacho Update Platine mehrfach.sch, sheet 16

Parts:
C16: 100nF; C0805
IC16: LM358D; SO08
R91, R92: 1002; R0805
R93, R95, R96: 102; R0805
R94: 2702; R0805

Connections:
GND: C16.2, R91.1, R96.1; also elsewhere on the board
unnamed: IC16.1 (OUT), R92.2
unnamed: C16.1, R92.1, R93.1
unnamed: IC16.5 (+IN), R93.2, R94.2
unnamed: IC16.6 (-IN), R95.1, R96.2
unnamed: IC16.2 (-IN), R91.2
unnamed: IC16.7 (OUT), R94.1
V+15: IC16.8 (V+)
V-15: IC16.4 (V-)
VCC: R95.2; also elsewhere on the board
